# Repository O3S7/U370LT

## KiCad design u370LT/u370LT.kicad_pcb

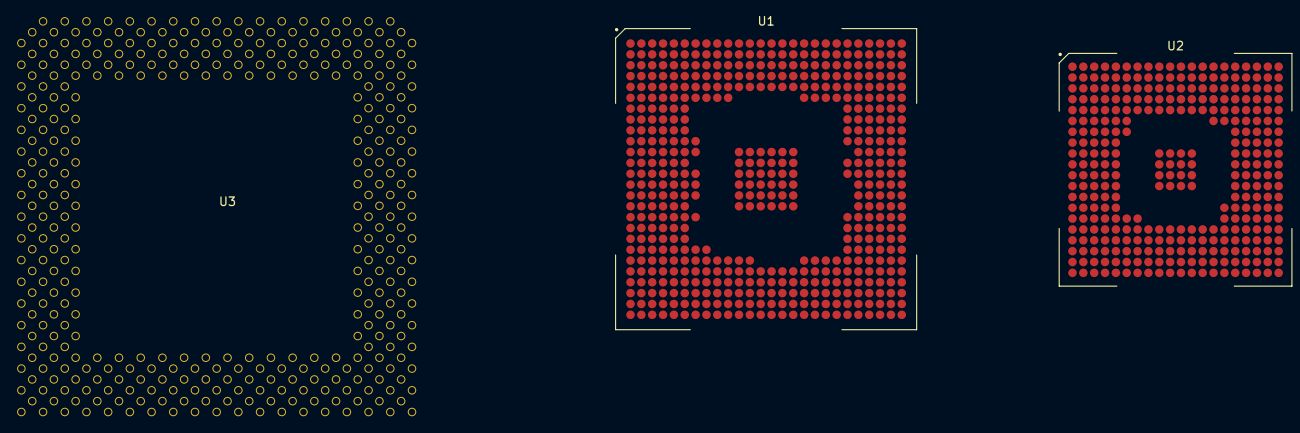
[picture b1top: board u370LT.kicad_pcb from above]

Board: 2 copper layers, 3 parts (0 on the bottom side), 43 nets, no tracks yet.

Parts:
U1: VT82C694X
U2: VT82C596B
U3: PGA370

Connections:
HA3: U1.G25 (HA3#), U3.AK8 (A3#)
HA4: U1.H22 (HA4#), U3.AH12 (A4#)
HA5: U1.G23 (HA5#), U3.AH8 (A5#)
HA7: U1.G24 (HA7#), U3.AL15 (A7#)
HA8: U1.F26 (HA08#), U3.AH10 (A8#)
HA9: U1.G26 (HA9#), U3.AL9 (A9#)
HA10: U1.G22 (HA10#), U3.AH6 (A10#)
HA11: U1.F22 (HA11#), U3.AK10 (A11#)
HA12: U1.F23 (HA12#), U3.AN5 (A12#)
HA13: U1.F24 (HA13#), U3.AL7 (A13#)
HA14: U1.F25 (HA14#), U3.AK14 (A14#)
HA16: U1.E26 (HA16#), U3.AN7 (A16#)
HA17: U1.E25 (HA17#), U3.AE1 (A17#)
HA18: U1.D25 (HA18#), U3.Z6 (A18#)
HA19: U1.D26 (HA19#), U3.AG3 (A19#)
HA20: U1.B25 (HA20#), U3.AC3 (A20#)
HA21: U1.C26 (HA21#), U3.AJ1 (A21#)
HA22: U1.A25 (HA22#), U3.AE3 (A22#)
HA23: U1.C25 (HA23#), U3.AB6 (A23#)
HA24: U1.A24 (HA24#), U3.AB4 (A24#)
HA25: U1.D24 (HA25#), U3.AF6 (A25#)
HA26: U1.C23 (HA26#), U3.Y3 (A26#)
HA27: U1.B24 (HA27#), U3.AA1 (A27#)
HA28: U1.C24 (HA28#), U3.AK6 (A28#)
HA29: U1.A23 (HA29#), U3.Z4 (A29#)
HA30: U1.E22 (HA30#), U3.AA3 (A30#)
HA31: U1.D23 (HA31#), U3.AD4 (A31#)
unnamed: U1.A1 (GND), U1.A14 (GND), U1.A26 (GND), U1.AA6 (GND), U1.AA8 (GND), U1.AA19 (GND), U1.AA21 (GND), U1.AB12 (GND), U1.AB15 (GND), U1.AB24 (GND), U1.AB25 (GND), U1.AC4 (GND), U1.AD9 (GND), U1.AD18 (GND), U1.AD22 (GND), U1.AE23 (GND), U1.AF1 (GND), U1.AF13 (GND), U1.AF26 (GND), U1.C5 (GND), U1.C9 (GND), U1.C18 (GND), U1.C22 (GND), U1.E3 (GND), U1.E12 (GND), U1.E15 (GND), U1.E24 (GND), U1.F6 (GND), U1.F8 (GND), U1.F19 (GND), U1.F21 (GND), U1.H6 (GND), U1.H21 (GND), U1.J3 (GND), U1.J24 (GND), U1.K1 (GND), U1.K7 (GND), U1.L12 (GND), U1.L15 (GND), U1.M11 (GND), U1.M13 (GND), U1.M14 (GND), U1.M16 (GND), U1.N7 (GND), U1.N12 (GND), U1.N13 (GND), U1.N14 (GND), U1.N15 (GND), U1.N24 (GND), U1.P3 (GND), U1.P7 (GND), U1.P12 (GND), U1.P13 (GND), U1.P14 (GND), U1.P15 (GND), U1.P22 (GND), U1.P26 (GND), U1.R11 (GND), U1.R13 (GND), U1.R14 (GND), U1.R16 (GND), U1.R22 (GND), U1.T12 (GND), U1.T15 (GND), U1.U6 (GND), U1.V24 (GND), U1.Y3 (GND), U1.Y6 (GND), U1.Y7 (GND), U1.Y8 (GND)
unnamed: U1.M21 (GNDA), U1.M22 (GNDA), U1.U7 (GNDA), U1.W21 (GNDA)
unnamed: U1.E16 (GTLREF), U1.M23 (GTLREF)
unnamed: U1.AA9 (VCC), U1.AA18 (VCC), U1.AA20 (VCC), U1.AE26 (VCC), U1.AF14 (VCC), U1.B1 (VCC), U1.C2 (VCC), U1.F7 (VCC), U1.F9 (VCC), U1.F18 (VCC), U1.F20 (VCC), U1.G6 (VCC), U1.G21 (VCC), U1.J6 (VCC), U1.J21 (VCC), U1.L11 (VCC), U1.L13 (VCC), U1.L14 (VCC), U1.L16 (VCC), U1.M12 (VCC), U1.M15 (VCC), U1.N11 (VCC), U1.N16 (VCC), U1.N26 (VCC), U1.P11 (VCC), U1.P16 (VCC), U1.R12 (VCC), U1.R15 (VCC), U1.T11 (VCC), U1.T13 (VCC), U1.T14 (VCC), U1.T16 (VCC), U1.V21 (VCC)
unnamed: U1.N21 (VCCA), U1.N22 (VCCA), U1.V6 (VCCA), U1.Y21 (VCCA)
unnamed: U1.AA3 (VCCQ), U1.AA7 (VCCQ), U1.L6 (VCCQ), U1.L7 (VCCQ), U1.R3 (VCCQ), U1.R6 (VCCQ), U1.R7 (VCCQ)
unnamed: U1.AD4 (VCCQQ), U1.W6 (VCCQ)
unnamed: U1.F17 (VTT), U1.M24 (VTT)
unnamed: U2.D10 (GND), U2.E7 (GND), U2.E13 (GND), U2.J9 (GND), U2.J10 (GND), U2.J11 (GND), U2.J12 (GND), U2.K9 (GND), U2.K10 (GND), U2.K11 (GND), U2.K12 (GND), U2.L9 (GND), U2.L10 (GND), U2.L11 (GND), U2.L12 (GND), U2.M9 (GND), U2.M10 (GND), U2.M11 (GND), U2.M12 (GND)
unnamed: U2.T8 (SA9), U2.V16 (DACK6#)
unnamed: U2.E9 (VCC), U2.E11 (VCC), U2.E12 (VCC), U2.E16 (VCC), U2.F5 (VCC), U2.F6 (VCC), U2.F14 (VCC), U2.F15 (VCC), U2.G6 (VCC), U2.P15 (VCC), U2.R6 (VCC), U2.R7 (VCC), U2.R15 (VCC), U2.T6 (VCC)
unnamed: U2.N16 (VCCSUS), U2.R16 (VCCSUS)
unnamed: U3.A37 (GND), U3.AB32 (GND), U3.AC5 (GND), U3.AC33 (GND), U3.AD2 (GND), U3.AD34 (GND), U3.AF32 (GND), U3.AF36 (GND), U3.AG5 (GND), U3.AH2 (GND), U3.AH34 (GND), U3.AJ3 (GND), U3.AJ7 (GND), U3.AJ11 (GND), U3.AJ15 (GND), U3.AJ19 (GND), U3.AJ23 (GND), U3.AJ27 (GND), U3.AK4 (GND), U3.AK36 (GND), U3.AL1 (GND), U3.AL3 (GND), U3.AM6 (GND), U3.AM10 (GND), U3.AM14 (GND), U3.AM18 (GND), U3.AM22 (GND), U3.AM26 (GND), U3.AM30 (GND), U3.AM34 (GND), U3.AN3 (GND), U3.B4 (GND), U3.B8 (GND), U3.B12 (GND), U3.B16 (GND), U3.B20 (GND), U3.B24 (GND), U3.B28 (GND), U3.B32 (GND), U3.D2 (GND), U3.D4 (GND), U3.D18 (GND), U3.D22 (GND), U3.D26 (GND), U3.D30 (GND), U3.D34 (GND), U3.E7 (GND), U3.E11 (GND), U3.E15 (GND), U3.E19 (GND), U3.F20 (GND), U3.F24 (GND), U3.F28 (GND), U3.F32 (GND), U3.F36 (GND), U3.G5 (GND), U3.H2 (GND), U3.H34 (GND), U3.K36 (GND), U3.L5 (GND), U3.M2 (GND), U3.M34 (GND), U3.P32 (GND), U3.P36 (GND), U3.Q5 (GND), U3.R34 (GND), U3.T32 (GND), U3.T36 (GND), U3.U5 (GND), U3.V2 (GND), U3.V34 (GND), U3.X32 (GND), U3.X36 (GND), U3.Y5 (GND), U3.Y37 (GND), U3.Z2 (GND), U3.Z34 (GND)
unnamed: U3.AA5 (VCCCORE), U3.AA37 (VCCCORE), U3.AB2 (VCCCORE), U3.AB34 (VCCCORE), U3.AD32 (VCCCORE), U3.AE5 (VCCCORE), U3.AF2 (VCCCORE), U3.AF34 (VCCCORE), U3.AH24 (VCCCORE), U3.AH32 (VCCCORE), U3.AH36 (VCCCORE), U3.AJ5 (VCCCORE), U3.AJ9 (VCCCORE), U3.AJ13 (VCCCORE), U3.AJ17 (VCCCORE), U3.AJ21 (VCCCORE), U3.AJ25 (VCCCORE), U3.AJ29 (VCCCORE), U3.AK2 (VCCCORE), U3.AK34 (VCCCORE), U3.AM4 (VCCCORE), U3.AM8 (VCCCORE), U3.AM12 (VCCCORE), U3.AM16 (VCCCORE), U3.AM20 (VCCCORE), U3.AM24 (VCCCORE), U3.AM28 (VCCCORE), U3.AM32 (VCCCORE), U3.B6 (VCCCORE), U3.B10 (VCCCORE), U3.B14 (VCCCORE), U3.B18 (VCCCORE), U3.B22 (VCCCORE), U3.B26 (VCCCORE), U3.B30 (VCCCORE), U3.B34 (VCCCORE), U3.C3 (VCCCORE), U3.D6 (VCCCORE), U3.D20 (VCCCORE), U3.D24 (VCCCORE), U3.D28 (VCCCORE), U3.D32 (VCCCORE), U3.D36 (VCCCORE), U3.E5 (VCCCORE), U3.E9 (VCCCORE), U3.E13 (VCCCORE), U3.E17 (VCCCORE), U3.F2 (VCCCORE), U3.F4 (VCCCORE), U3.F14 (VCCCORE), U3.F22 (VCCCORE), U3.F26 (VCCCORE), U3.F30 (VCCCORE), U3.F34 (VCCCORE), U3.H32 (VCCCORE), U3.H36 (VCCCORE), U3.J5 (VCCCORE), U3.K2 (VCCCORE), U3.K32 (VCCCORE), U3.K34 (VCCCORE), U3.M32 (VCCCORE), U3.N5 (VCCCORE), U3.P2 (VCCCORE), U3.P34 (VCCCORE), U3.R32 (VCCCORE), U3.R36 (VCCCORE), U3.S5 (VCCCORE), U3.T2 (VCCCORE), U3.T34 (VCCCORE), U3.V32 (VCCCORE), U3.V36 (VCCCORE), U3.W5 (VCCCORE), U3.Y35 (VCCCORE), U3.Z32 (VCCCORE)
unnamed: U3.AD6 (VREF), U3.AK12 (VREF), U3.AK22 (VREF), U3.F18 (VREF), U3.K4 (VREF), U3.R6 (VREF), U3.V6 (VREF)
unnamed: U3.AA33 (VTT), U3.AA35 (VTT), U3.AD36 (VTT), U3.AH20 (VTT), U3.AK16 (VTT), U3.AL13 (VTT), U3.AL21 (VTT), U3.AN11 (VTT), U3.AN15 (VTT), U3.AN21 (VTT), U3.E23 (VTT), U3.G35 (VTT), U3.S33 (VTT), U3.S37 (VTT), U3.U35 (VTT), U3.U37 (VTT)

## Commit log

2024-06-18 Push inital KiCAD files
2024-06-23 Updated northbridge more
2024-07-05 NB fixed up, SB started
2024-07-07 More chipset work
2024-09-08 Got NB/SB initially placed
2024-11-21 More NB work
2024-11-21 Pushing start of PGA370 info
2024-11-25 More 370 work
